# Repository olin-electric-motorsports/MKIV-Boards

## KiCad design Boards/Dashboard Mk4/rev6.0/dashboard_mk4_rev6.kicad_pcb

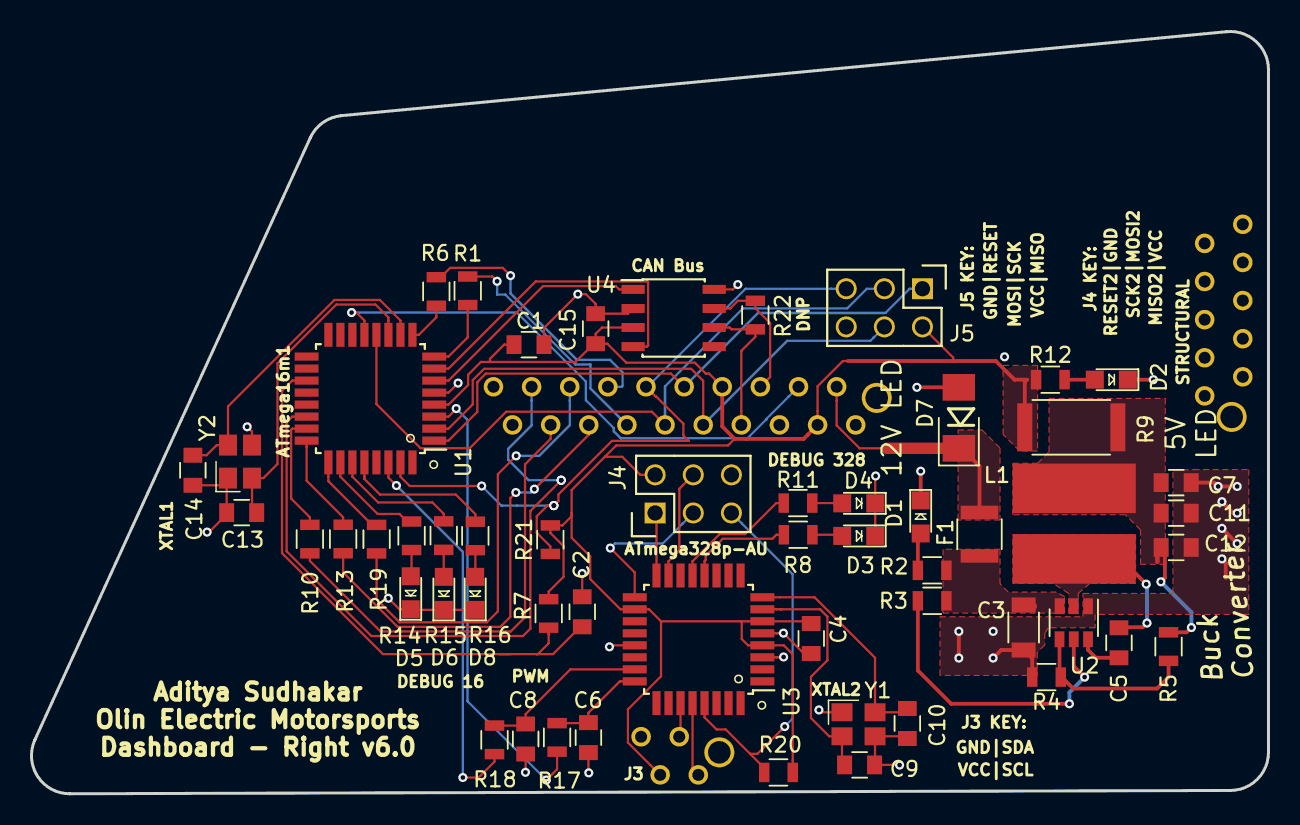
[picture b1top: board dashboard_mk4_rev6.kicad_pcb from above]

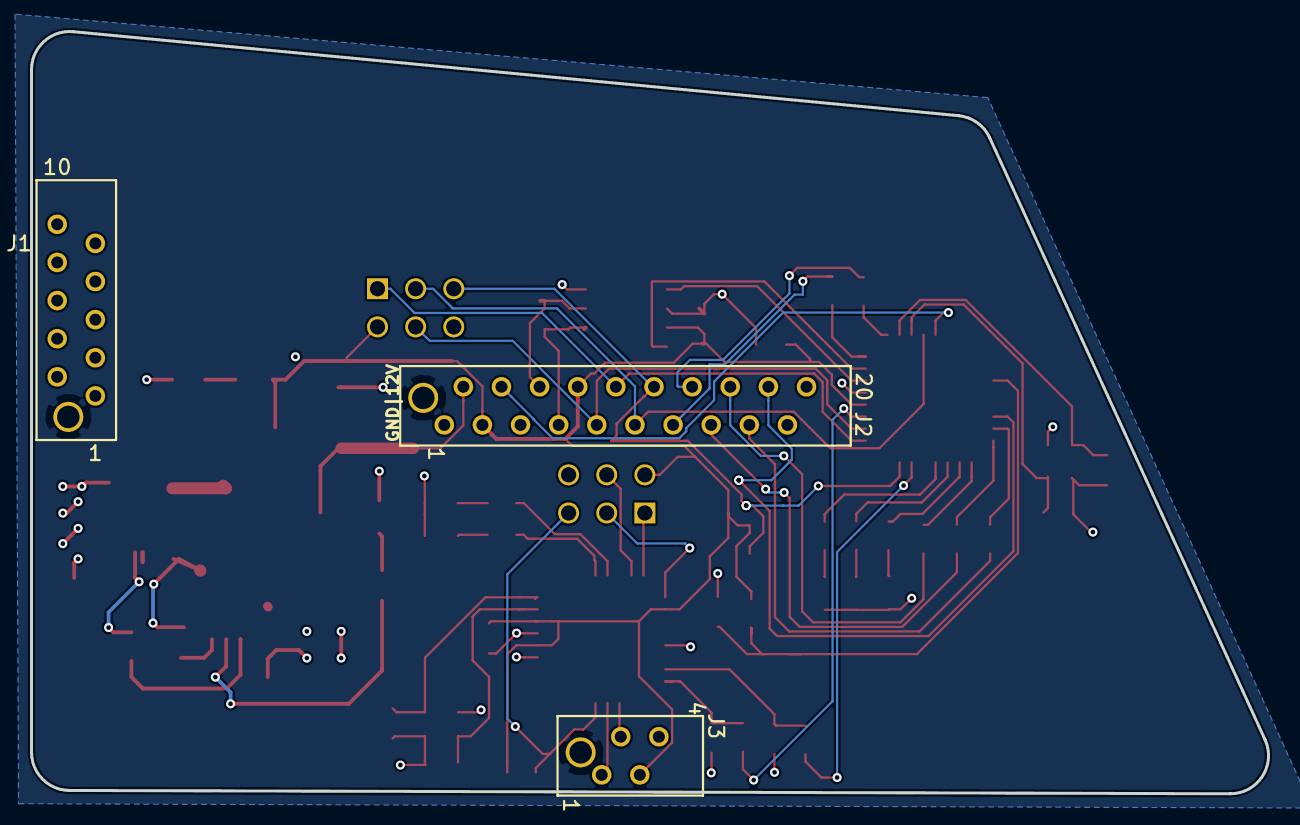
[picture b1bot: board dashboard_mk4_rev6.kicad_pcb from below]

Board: 2 copper layers, 82.4 x 50.8 mm, 58 parts (3 on the bottom side), 56 nets.

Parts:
C1, C4, C5, C6, C7, C8, C15: C_0.1uF; C_0805_OEM
C2: C_100pF; C_0805_OEM
C3: C_22uF; C_1206_OEM
C9, C10, C13, C14: C_30pF; C_0805_OEM
C11: C_1uF; C_0805_OEM
C12: C_47uF; C_0805_OEM
D1, D2: LED_0805; LED_0805_OEM
D3, D4, D5, D6, D8: LED; LED_0805_OEM
D7: D_Zener_18V; DO-214AA
F1: 500mA; Fuse_1210
J1: MM_F_VT_10; micromatch_female_vert_10
J2: MM_F_VT_20; micromatch_female_vert_20
J3: MM_F_VT_04; micromatch_female_vert_4
J4, J5: CONN_02X03; Pin_Header_Straight_2x03
L1: L_4.7uH; 4.7uH_Inductor_OEM
R1, R6, R8, R10, R11, R12, R13, R14, R15, R16, R19: R_200; R_0805_OEM
R2: R_1k; R_0805_OEM
R3, R4, R21: R_10k; R_0805_OEM
R5: R_51.1k; R_0805_OEM
R7: R_100; R_0805_OEM
R9: R_0_Jumper; R_2512_OEM
R17, R18: R_100K; R_0805_OEM
R20: R_10K; R_0805_OEM
R22: R_120; R_0805_OEM
U1: ATMEGA16M1; TQFP-32_7x7mm_Pitch0.8mm
U2: TPS561201; SOT-23-6_OEM
U3: ATmega328P-AU; TQFP-32_7x7mm_Pitch0.8mm
U4: CAN_Transceiver; SOIC-8_3.9x4.9mm_Pitch1.27mm_OEM
Y1, Y2: Crystal_SMD; Crystal_SMD_FA238

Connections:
+12V: D7.1, F1.1, J2.2
/12V_Fused: C3.1, F1.2, R2.1, R3.1, U2.3
/CANH: J2.6, R22.1, U4.7
/CANL: J2.7, R22.2, U4.6
/LED_BMS: J2.16, R19.2
/LED_IMD: J2.17, R10.1
/LED_START: J2.15, R13.1
/MISO: J2.10, J5.1, U1.1
/MISO_2: J4.1, U3.16
/MOSI: J2.9, J5.4, U1.2
/MOSI_2: J4.4, U3.15
/PWM_0: R18.1, U1.30
/PWM_1: R17.1, U1.3
/RESET: J2.12, J5.5, R21.1, U1.31
/RESET_2: J4.5, R20.1, U3.29
/RJLED1: J2.13, R1.1
/RJLED2: J2.14, R6.1
/RXCAN: U1.7, U4.4
/SCK: J2.11, J5.3, U1.12
/SCK_2: J4.3, U3.17
/SCL: J3.1, U3.28
/SDA: J3.2, U3.27
/START_BTN: J2.18, U1.22
/STR_POT_SENSE: J2.4, U1.13
/TXCAN: U1.6, U4.1
/XTAL1: C9.1, U3.7, Y1.1
/XTAL2: C10.1, U3.8, Y1.3
GND: C1.2, C2.2, C3.2, C4.2, C6.2, C7.2, C8.2, C9.2, C10.2, C11.2, C12.2, C13.2, C14.2, C15.2, D1.1, D2.1, D3.1, D4.1, D5.1, D6.1, D7.2, D8.1, J2.1, J2.5, J3.4, J4.6, J5.6, R4.2, U1.5, U2.1, U3.3, U3.5, U3.21, U4.2, U4.8, Y1.2, Y1.4, Y2.2, Y2.4
unnamed: C2.1, R7.2, U1.19
unnamed: C5.1, U2.6
unnamed: C5.2, L1.1, U2.2
unnamed: C6.1, R17.2, U3.24
unnamed: C8.1, R18.2, U3.23
unnamed: C7.1, C11.1, C12.1, L1.2, R5.2, R9.2
unnamed: C13.1, U1.11, Y2.1
unnamed: C14.1, U1.10, Y2.3
unnamed: D1.2, R2.2
unnamed: D2.2, R12.2
unnamed: D3.2, R8.1
unnamed: D4.2, R11.1
unnamed: D5.2, R14.2
unnamed: D6.2, R15.2
unnamed: D8.2, R16.2
unnamed: R1.2, U1.8
unnamed: R3.2, U2.5
unnamed: R4.1, R5.1, U2.4
unnamed: R6.2, U1.9
unnamed: R8.2, U3.12
unnamed: R10.2, U1.23
unnamed: R11.2, U3.13
unnamed: R13.2, U1.24
unnamed: R14.1, U1.26
unnamed: R15.1, U1.27
unnamed: R16.1, U1.28
unnamed: R19.1, U1.25
VCC: C1.1, C4.1, C15.1, J2.3, J2.8, J3.3, J4.2, J5.2, R7.1, R9.1, R12.1, R20.2, R21.2, U1.4, U3.4, U3.6, U3.18, U4.3

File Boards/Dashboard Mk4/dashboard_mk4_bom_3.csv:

Component,Description,Part,References,Value,Footprint,Quantity Per PCB,Datasheet,Package,MPN,MFN,PurchasingLink
1,"Capacitor, 0.1uF, 50V, 5%, 0805",C_0.1uF,C1 C4 C5 C6 C7 C8 C15,C_0.1uF,C_0805_OEM,7,http://datasheets.avx.com/X7RDielectric.pdf,Value,478-3352-1-ND,DK,https://www.digikey.com/products/en?keywords=478-3352-1-ND
2,"Capacitor, 100pF, 50V, 5%, 0805",C_100pF,C2,C_100pF,C_0805_OEM,1,https://katalog.we-online.de/pbs/datasheet/885012007057.pdf,Value,732-7852-1-ND,DK,https://www.digikey.com/product-detail/en/wurth-electronics-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
3,"Capacitor, 1uF, 25V, 10%, 0805",C_1uF,C11,C_1uF,C_0805_OEM,1,http://www.samsungsem.com/kr/support/product-search/mlcc/__i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,Value,1276-2887-1-ND,DK,https://www.digikey.com/product-detail/en/samsung-electro-me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
4,"Capacitor, 22uF, 16V, 20%, 1206",C_22uF,C3,C_22uF,C_1206_OEM,1,https://product.tdk.com/info/en/catalog/datasheets/mlcc_comm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,Value,445-11693-1-ND,DK,https://www.digikey.com/product-detail/en/tdk-corporation/C3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
5,"Capacitor, 30pF, 50V, 5%, 0805",C_30pF,C9 C10 C13 C14,C_30pF,C_0805_OEM,4,https://media.digikey.com/pdf/Data%20Sheets/Samsung%20PDFs/C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,Value,1276-1130-1-ND,DK,https://www.digikey.com/product-detail/en/samsung-electro-me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
6,"Capacitor, 47uF, 6.3V, 20%, 0805",C_47uF,C12,C_47uF,C_0805_OEM,1,http://www.samsungsem.com/kr/support/product-search/mlcc/__i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,Value,1276-6467-1-ND,DK,https://www.digikey.com/product-detail/en/samsung-electro-me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
7,"Diode, Zener, 18V, 5W, 5%",D_Zener_18V,D7,D_Zener_18V,DO-214AA,1,http://www.mccsemi.com/up_pdf/SMBJ5338B-SMBJ5388B(SMB).pdf,DO-214AA (SMB),SMBJ5355B-TPMSCT-ND,DK,https://www.digikey.com/products/en?keywords=SMBJ5355B-TPMSCT-ND
8,Light emitting diode,LED,D3 D4 D5 D6 D8,LED,LED_0805_OEM,5,,,,,
9,"LED, Green, 2.2V, 20mA, 0805",LED_0805,D1 D2,LED_0805,LED_0805_OEM,2,http://www.osram-os.com/Graphics/XPic9/00078860_0.pdf,Value,475-1410-1-ND,DK,https://www.digikey.com/products/en?keywords=475-1410-1-ND
10,"Fuse, PTC, 500mA, 16V, 1210",F_500mA_16V,F1,500mA,Fuse_1210,1,https://belfuse.com/resources/CircuitProtection/datasheets/0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,Value,507-1786-1-ND,DK,https://www.digikey.com/product-detail/en/bel-fuse-inc/0ZCH0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
11,"Connector header through hole 2x3 0.100"" (2.54mm)",CONN_02X03,J4 J5,CONN_02X03,Pin_Header_Straight_2x03,2,http://portal.fciconnect.com/Comergent//fci/drawing/67996.pdf,Value,609-3234-ND,DK,https://www.digikey.com/product-detail/en/amphenol-fci/67997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
12,Micro-MaTch connector 4 pin female vertical,MM_F_VT_04,J3,MM_F_VT_04,micromatch_female_vert_4,1,http://www.te.com/commerce/DocumentDelivery/DDEController?Ac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,,338068-4,TE,http://www.te.com/global-en/product-338068-4.html
13,Micro-MaTch connector 10 pin female vertical,MM_F_VT_10,J1,MM_F_VT_10,micromatch_female_vert_10,1,http://www.te.com/commerce/DocumentDelivery/DDEController?Ac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,,1-338068-0,TE,http://www.te.com/global-en/product-1-338068-0.html
14,Micro-MaTch connector 20 pin female vertical,MM_F_VT_20,J2,MM_F_VT_20,micromatch_female_vert_20,1,http://www.te.com/commerce/DocumentDelivery/DDEController?Ac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,,2-338068-0,TE,http://www.te.com/global-en/product-2-338068-0.html
15,"Inductor, 4.7uH, 4.4A, 25mOhm, 20%",L_4.7uH,L1,L_4.7uH,4.7uH_Inductor_OEM,1,https://product.tdk.com/info/en/documents/wdcatalog/withdraw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,Value,445-6583-1-ND,DK,https://www.digikey.com/product-detail/en/tdk-corporation/VL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
16,"Resistor, 0 ohm jumper, 0.1W, 0603",R_0,R9,R_0_Jumper,R_0603_1608Metric,1,http://industrial.panasonic.com/www-cgi/jvcr13pz.cgi?E+PZ+3+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,Value,P0.0GCT-ND,DK,https://www.digikey.com/product-detail/en/panasonic-electron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
17,"Resistor, 100, 0.25W, 1%, 0805",R_100,R7,R_100,R_0805_OEM,1,https://www.seielect.com/Catalog/SEI-rncp.pdf,Value,RNCP0805FTD100RCT-ND,DK,https://www.digikey.com/products/en?keywords=RNCP0805FTD100RCT-ND
18,"Resistor, 100K, 0.125W, 1%, 0805",R_100K,R17 R18,R_100K,R_0805_OEM,2,https://industrial.panasonic.com/cdbs/www-data/pdf/RDA0000/A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,,P100KCCT-ND,DK,https://www.digikey.com/product-detail/en/panasonic-electron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
19,"Resistor, 10K, 0.25W, 1%, 0805",R_10K,R20 R21,R_10K,R_0805_OEM,2,http://www.bourns.com/data/global/pdfs/CRS.pdf,Value,CRS0805-FX-1002ELFCT-ND,DK,https://www.digikey.com/products/en?keywords=CRS0805-FX-1002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
20,"Resistor, 10K, 5W, 1%, Axial",R_10K_HV,R3 R4,R_10k,R_1K_HV,2,http://www.vishay.com/docs/28731/pacserie.pdf,Value,PPC5D10.0KCT-ND,DK,https://www.digikey.com/products/en?keywords=PPC5D10.0KCT-ND
21,"Resistor, 200, 0.125W, 5%, 0805",R_200,R22,R_120,R_0805_OEM,1,https://www.seielect.com/Catalog/SEI-RMCF_RMCP.pdf,Value,RMCF0805JT200RCT-ND,DK,https://www.digikey.com/products/en?keywords=RMCF0805JT200RCT-ND
22,"Resistor, 1K, 0.25W, 1%, 0805",R_1K,R2,R_1k,R_0805_OEM,1,https://www.seielect.com/Catalog/SEI-rncp.pdf,Value,RNCP0805FTD1K00CT-ND,DK,https://www.digikey.com/products/en?keywords=RNCP0805FTD1K00CT-ND
23,"Resistor, 200, 0.125W, 5%, 0805",R_200,R1 R6 R8 R10 R11 R12 R13 R14 R15 R16 R19,R_200,R_0805_OEM,11,https://www.seielect.com/Catalog/SEI-RMCF_RMCP.pdf,Value,RMCF0805JT200RCT-ND,DK,https://www.digikey.com/products/en?keywords=RMCF0805JT200RCT-ND
24,"Resistor, 51.1K, 0.125W, 1%, 0805",R_51.1K,R5,R_51.1k,R_0805_OEM,1,https://industrial.panasonic.com/cdbs/www-data/pdf/RDA0000/A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,Value,P51.1KCCT-ND,DK,https://www.digikey.com/product-detail/en/panasonic-electron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
25,"Microcontroller, 8-bit, 1KB RAM, 16KB Flash",ATMEGA16M1,U1,ATMEGA16M1,TQFP-32_7x7mm_Pitch0.8mm,1,http://ww1.microchip.com/downloads/en/DeviceDoc/Atmel-8209-8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,,ATMEGA16M1-AU-ND,DK,https://www.digikey.com/product-detail/en/atmel/ATMEGA16M1-A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
26,"Microcontroller, 8-bit, 1KB RAM, 16KB Flash",ATmega328P-AU,U3,ATmega328P-AU,TQFP-32_7x7mm_Pitch0.8mm,1,http://ww1.microchip.com/downloads/en/DeviceDoc/Atmel-7810-A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,,ATMEGA328P-AURCT-ND,,https://www.digikey.com/product-detail/en/microchip-technolo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
27,"High speed CAN transceiver, 1Mb/s",MCP2561-E_SN,U4,CAN_Transceiver,SOIC-8_3.9x4.9mm_Pitch1.27mm_OEM,1,http://www.microchip.com/mymicrochip/filehandler.aspx?ddocna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,Value,MCP2561-E/SN-ND,DK,https://www.digikey.com/products/en?keywords=mcp2561-e%2Fsn
28,"Buck converter, 4.5-17V input, adj 0.76-7V output, 1A, 580kHz",TPS561201,U2,TPS561201,SOT-23-6_OEM,1,http://www.ti.com/lit/ds/symlink/tps561201.pdf,Value,TPS561201,DK,https://www.digikey.com/products/en?keywords=296-46928-1-ND
29,CRYSTAL 16.0000MHZ 18PF SMD,Crystal_SMD,Y1 Y2,Crystal_SMD,Crystal_SMD_FA238,2,http://www.txccorp.com/download/products/quartz_crystals/201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,Value,887-1125-1-ND,DK,https://www.digikey.com/product-detail/en/txc-corporation/7M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





Component Groups:,29
Component Count:,58
Fitted Components:,58
Number of PCBs:,1
Total components:,58
Schematic Version:,3
Schematic Date:,
BoM Date:,Tue 20 Nov 2018 10:55:47 AM EST
Schematic Source:,/home/asudhakar/Documents/Forumla/MKIV-Boards/Boards/Dashboard Mk4/dashboard_mk4.sch
KiCad Version:,Eeschema 5.0.1-33cea8e~68~ubuntu18.04.1

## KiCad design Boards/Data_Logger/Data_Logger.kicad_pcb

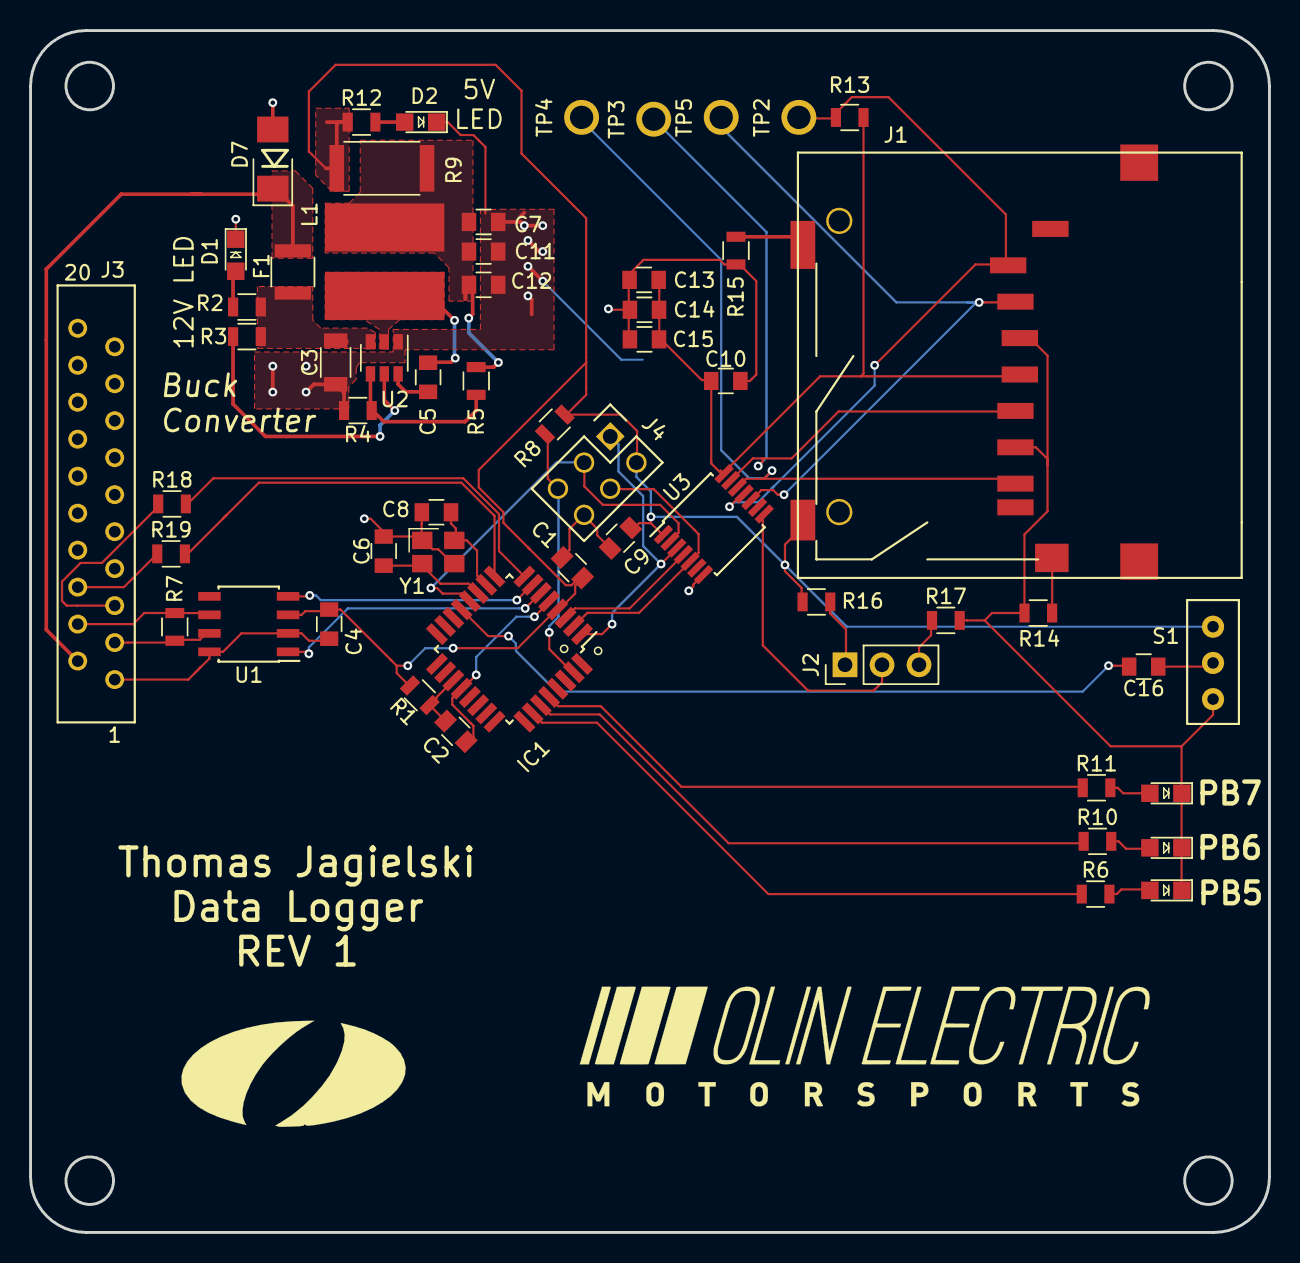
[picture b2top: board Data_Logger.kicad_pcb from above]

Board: 2 copper layers, 85.1 x 82.6 mm, 57 parts (0 on the bottom side), 45 nets.

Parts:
C1, C4, C5, C9, C10, C12, C15, C16: C_0.1uF; C_0805_OEM
C2: C_100pF; C_0805_OEM
C3: C_22uF; C_1206_OEM
C6, C8: C_30pF; C_0805_OEM
C7: C_47uF; C_0805_OEM
C11, C14: C_1uF; C_0805_OEM
C13: C_10uF; C_0805_OEM
D1, D2, D3, D4, D5: LED_0805; LED_0805_OEM
D7: D_Zener_18V; DO-214AA
F1: 500mA; Fuse_1210
IC1: ATMEGA16M1; TQFP-32_7x7mm_Pitch0.8mm
J1: SD_socket; sd_socket_molex_5009980900
J2: Conn_01x03; PinHeader_1x03_P2.54mm_Vertical
J3: MM_F_RA_20; micromatch_female_ra_20
J4: CONN_02X03; Pin_Header_Straight_2x03
L1: L_4.7uH; 4.7uH_Inductor_OEM
R1: R_100; R_0805_OEM
R2: R_1k; R_0805_OEM
R3, R4, R8: R_10k; R_0805_OEM
R5: R_51.1k; R_0805_OEM
R6, R10, R11, R12, R18, R19: R_200; R_0805_OEM
R7: R_120; R_0805_OEM
R9: R_0_Jumper; R_2512_OEM
R13, R14, R15, R16, R17: R_10K; R_0805_OEM
S1: MHSS1105
TP2, TP3, TP4, TP5: TP; tp_1.6mm
U1: CAN_Transceiver; SOIC-8_3.9x4.9mm_Pitch1.27mm_OEM
U2: TPS561201; SOT-23-6_OEM
U3: TXB0104; TSSOP-14_4.4x5mm_P0.65mm
Y1: Crystal_SMD; Crystal_SMD_FA238

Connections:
+3V3: C10.1, C13.1, C14.1, C15.1, J1.4, R13.1, U3.14
+12V: D7.1, F1.1, J3.2
/12V_Fused: C3.1, F1.2, R2.1, R3.1, U2.3
/CANH: J3.3, R7.1, U1.7
/CANL: J3.4, R7.2, U1.6
/LED_1: J3.5, R18.1
/LED_2: J3.6, R19.1
/MISO: IC1.1, J4.1, U3.3
/MISO_3V3: J1.7, TP4.1, U3.12
/MOSI: IC1.2, J4.4, U3.5
/MOSI_3V3: J1.2, TP5.1, U3.10
/PLED1: IC1.26, R6.1
/PLED2: IC1.27, R10.1
/PLED3: IC1.28, R11.1
/RESET: IC1.31, J4.5, R8.2
/RXCAN: IC1.7, U1.4
/SCK: IC1.12, J4.3, U3.2
/SCK_3V3: J1.5, TP3.1, U3.13
/SS: IC1.3, U3.4
/SS_3V3: J1.1, R13.2, TP2.1, U3.11
/SWITCH: C16.2, IC1.13
/TXCAN: IC1.6, U1.1
GND: C1.2, C2.2, C3.2, C4.2, C6.2, C7.2, C8.2, C9.2, C10.2, C11.2, C12.2, C13.2, C14.2, C15.2, D1.1, D2.1, D3.1, D4.1, D5.1, D7.2, IC1.5, IC1.20, J1.3, J1.6, J3.1, J4.6, R4.2, R14.2, R15.2, R17.2, S1.3, U1.2, U1.8, U2.1, U3.7, Y1.2, Y1.4
unnamed: C2.1, IC1.19, R1.2
unnamed: C5.1, U2.6
unnamed: C5.2, L1.1, U2.2
unnamed: C6.1, IC1.11, Y1.1
unnamed: C8.1, IC1.10, Y1.3
unnamed: C7.1, C11.1, C12.1, L1.2, R5.2, R9.2
unnamed: C16.1, S1.2
unnamed: D1.2, R2.2
unnamed: D2.2, R12.2
unnamed: D3.2, R6.2
unnamed: D4.2, R10.2
unnamed: D5.2, R11.2
unnamed: IC1.8, R18.2
unnamed: IC1.9, R19.2
unnamed: J1.11, R14.1
unnamed: J1.12, R15.1
unnamed: J2.1, R16.2
unnamed: J2.2, U3.8
unnamed: J2.3, R17.1
unnamed: R3.2, U2.5
unnamed: R4.1, R5.1, U2.4
VCC: C1.1, C4.1, C9.1, IC1.4, J1.10, J4.2, R1.1, R8.1, R9.1, R12.1, R16.1, S1.1, U1.3, U3.1

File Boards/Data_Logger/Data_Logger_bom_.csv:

Component,Description,Part,References,Value,Footprint,Quantity Per PCB,Datasheet,Package,MPN,MFN,PurchasingLink,Purchasing Link
1,"Capacitor, 0.1uF, 50V, 5%, 0805",C_0.1uF,C1 C4 C5 C9 C10 C12 C15 C16,C_0.1uF,C_0805_OEM,8,http://datasheets.avx.com/X7RDielectric.pdf,Value,478-3352-1-ND,Digi-Key DK,https://www.digikey.com/products/en?keywords=478-3352-1-ND,
2,"Capacitor, 100pF, 50V, 5%, 0805",C_100pF,C2,C_100pF,C_0805_OEM,1,https://content.kemet.com/datasheets/KEM_C1003_C0G_SMD.pdf,Value,399-1122-1-ND,Digi-Key,https://www.digikey.com/product-detail/en/kemet/C0805C101J5G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,
3,"Capacitor, 10uF, 10V, 10%, 0805",C_10uF,C13,C_10uF,C_0805_OEM,1,http://www.samsungsem.com/kr/support/product-search/mlcc/__i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,,1276-1052-1-ND,DK,https://www.digikey.com/product-detail/en/samsung-electro-me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,
4,"Capacitor, 1uF, 25V, 10%, 0805",C_1uF,C11 C14,C_1uF,C_0805_OEM,2,http://datasheets.avx.com/X7RDielectric.pdf,Value,478-10487-1-ND 1276-2887-1-ND,Digi-Key DK,https://www.digikey.com/product-detail/en/avx-corporation/08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 https://www.digikey.com/product-detail/en/samsung-electro-me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,
5,"Capacitor, 22uF, 16V, 20%, 1206",C_22uF,C3,C_22uF,C_1206_OEM,1,http://www.samsungsem.com/kr/support/product-search/mlcc/__i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,Value,1276-2725-1-ND,Digi-Key,https://www.digikey.com/products/en?keywords=1276-2725-1-ND,
6,"Capacitor, 30pF, 50V, 5%, 0805",C_30pF,C6 C8,C_30pF,C_0805_OEM,2,https://media.digikey.com/pdf/Data%20Sheets/Samsung%20PDFs/C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,Value,1276-1130-1-ND,Digi-Key,https://www.digikey.com/product-detail/en/samsung-electro-me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,
7,"Capacitor, 47uF, 6.3V, 20%, 0805",C_47uF,C7,C_47uF,C_0805_OEM,1,http://www.yuden.co.jp/productdata/catalog/en/mlcc_all_e.pdf,Value,587-4280-1-ND,Digi-Key,https://www.digikey.com/product-detail/en/taiyo-yuden/JMK212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,
8,"Diode, Zener, 18V, 5W, 5%",D_Zener_18V,D7,D_Zener_18V,DO-214AA,1,http://www.mccsemi.com/up_pdf/SMBJ5338B-SMBJ5388B(SMB).pdf,DO-214AA (SMB),SMBJ5355B-TPMSCT-ND,Digi-Key,https://www.digikey.com/products/en?keywords=SMBJ5355B-TPMSCT-ND,
9,"LED, Green, 2.2V, 20mA, 0805",LED_0805,D1 D2 D3 D4 D5,LED_0805,LED_0805_OEM,5,http://www.osram-os.com/Graphics/XPic9/00078860_0.pdf,Value,475-1410-1-ND,Digi-Key DK,https://www.digikey.com/products/en?keywords=475-1410-1-ND,
10,"Fuse, PTC, 500mA, 16V, 1210",F_500mA_16V,F1,500mA,Fuse_1210,1,https://belfuse.com/resources/CircuitProtection/datasheets/0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,Value,507-1786-1-ND,Digi-Key,https://www.digikey.com/product-detail/en/bel-fuse-inc/0ZCH0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,
11,"Microcontroller, 8-bit, 1KB RAM, 16KB Flash",ATMEGA16M1,IC1,ATMEGA16M1,TQFP-32_7x7mm_Pitch0.8mm,1,http://www.atmel.com/Images/Atmel-8209-8-bit%20AVR%20ATmega1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,Value,ATMEGA16M1-AU-ND,Digi-Key,https://www.digikey.com/product-detail/en/atmel/ATMEGA16M1-A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,
12,"Connector header through hole 2x3 0.100"" (2.54mm)",CONN_02X03,J4,CONN_02X03,Pin_Header_Straight_2x03,1,http://portal.fciconnect.com/Comergent//fci/drawing/67996.pdf,Value,609-3234-ND,Digi-Key,https://www.digikey.com/product-detail/en/amphenol-fci/67997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,
13,"Generic connector, single row, 01x03, script generated (kicad-library-utils/schlib/autogen/connector/)",Conn_01x03,J2,Conn_01x03,PinHeader_1x03_P2.54mm_Vertical,1,~,,,,,
14,Micro-MaTch connector 20 pin female right angle,MM_F_RA_20,J3,MM_F_RA_20,micromatch_female_ra_20,1,http://www.te.com/commerce/DocumentDelivery/DDEController?Ac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,,2-338070-0,TE,http://www.te.com/usa-en/product-2-338070-0.html,
15,SD card socket with detect switch,SD_socket,J1,SD_socket,sd_socket_molex_5009980900,1,https://www.molex.com/pdm_docs/sd/5009980900_sd.pdf,,WM24032CT-ND,DK,https://www.digikey.com/product-detail/en/molex-llc/50099809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,
16,"Inductor, 4.7uH, 4.4A, 25mOhm, 20%",L_4.7uH,L1,L_4.7uH,4.7uH_Inductor_OEM,1,https://product.tdk.com/info/en/documents/wdcatalog/withdraw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,Value,445-6583-1-ND,Digi-Key,https://www.digikey.com/product-detail/en/tdk-corporation/VL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,
17,"Resistor, 0 ohm jumper, 0.1W, 0603",R_0,R9,R_0_Jumper,R_2512_OEM,1,http://www.te.com/commerce/DocumentDelivery/DDEController?Ac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,Value,A121322CT-ND,Digi-Key,https://www.digikey.com/products/en?keywords=A121322CT-ND,
18,"Resistor, 100, 0.25W, 1%, 0805",R_100,R1,R_100,R_0805_OEM,1,https://www.seielect.com/Catalog/SEI-rncp.pdf,Value,RNCP0805FTD100RCT-ND,Digi-Key,https://www.digikey.com/products/en?keywords=RNCP0805FTD100RCT-ND,
19,"Resistor, 10K, 0.25W, 1%, 0805",R_10K,R8 R13 R14 R15 R16 R17,R_10k,R_0805_OEM,6,http://www.bourns.com/data/global/pdfs/CRS.pdf,Value,CRS0805-FX-1002ELFCT-ND,Digi-Key DK,https://www.digikey.com/products/en?keywords=CRS0805-FX-1002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,
20,"Resistor, 10K, 5W, 1%, Axial",R_10K_HV,R3 R4,R_10k,R_0805_OEM,2,http://www.bourns.com/data/global/pdfs/CRS.pdf,Value,CRS0805-FX-1002ELFCT-ND,Digi-Key,https://www.digikey.com/products/en?keywords=CRS0805-FX-1002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,
21,"Resistor, 120, 0.125W, 1%, 0805",R_120,R7,R_120,R_0805_OEM,1,https://www.mouser.com/datasheet/2/315/AOA0000C304-1149620.pdf,,667-ERJ-6ENF1200V,DK,https://www.mouser.com/ProductDetail/Panasonic-Industrial-De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,
22,"Resistor, 1K, 0.25W, 1%, 0805",R_1K,R2,R_1k,R_0805_OEM,1,https://www.seielect.com/Catalog/SEI-rncp.pdf,Value,RNCP0805FTD1K00CT-ND,Digi-Key,https://www.digikey.com/products/en?keywords=RNCP0805FTD1K00CT-ND,
23,"Resistor, 200, 0.125W, 5%, 0805",R_200,R6 R10 R11 R12 R18 R19,R_200,R_0805_OEM,6,https://www.seielect.com/Catalog/SEI-RMCF_RMCP.pdf,Value,RMCF0805JT200RCT-ND,DK Digi-Key,https://www.digikey.com/products/en?keywords=RMCF0805JT200RCT-ND,
24,"Resistor, 51.1K, 0.125W, 1%, 0805",R_51.1K,R5,R_51.1k,R_0805_OEM,1,http://www.yageo.com.tw/exep/pages/download/literatures/PYu-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,Value,311-51.1KCRCT-ND,Digi-Key,https://www.digikey.com/products/en?keywords=311-51.1KCRCT-ND,
25,Slider Switch,MHSS1105,S1,MHSS1105,MHSS1105,1,https://www.apem.com/us/index.php?controller=attachment&id_a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,,679-1849-ND,APEM Inc.,,https://www.digikey.com/product-detail/en/apem-inc/MHSS1105/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
26,"High speed CAN transceiver, 1Mb/s",MCP2561-E_SN,U1,CAN_Transceiver,SOIC-8_3.9x4.9mm_Pitch1.27mm_OEM,1,http://www.microchip.com/mymicrochip/filehandler.aspx?ddocna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,Value,MCP2561-E/SN-ND,Digi-Key,https://www.digikey.com/products/en?keywords=mcp2561-e%2Fsn,
27,"Buck converter, 4.5-17V input, adj 0.76-7V output, 1A, 580kHz",TPS561201,U2,TPS561201,SOT-23-6_OEM,1,http://www.ti.com/lit/ds/symlink/tps561201.pdf,Value,TPS561201,Digi-Key,https://www.digikey.com/products/en?keywords=296-46928-1-ND,
28,"Voltage level translator, 4-channel, bidirectional, TSSOP-14",TXB0104,U3,TXB0104,TSSOP-14_4.4x5mm_P0.65mm,1,http://www.ti.com/lit/ds/symlink/txb0104.pdf,,296-21929-1-ND,DK,https://www.digikey.com/product-detail/en/texas-instruments/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,
29,CRYSTAL 16.0000MHZ 18PF SMD,Crystal_SMD,Y1,Crystal_SMD,Crystal_SMD_FA238,1,https://support.epson.biz/td/api/doc_check.php?dl=brief_FA-2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,Value,SER3686CT-ND,Digi-Key,https://www.digikey.com/products/en?keywords=SER3686CT-ND,





Component Groups:,29
Component Count:,53
Fitted Components:,53
Number of PCBs:,1
Total components:,53
Schematic Version:,
Schematic Date:,
BoM Date:,Thu 31 Jan 2019 08:48:02 PM EST
Schematic Source:,/home/thomas/Documents/Formula/MKIV-Boards/Boards/Data_Logger/Data_Logger.sch
KiCad Version:,Eeschema 5.0.2-bee76a0~70~ubuntu18.04.1

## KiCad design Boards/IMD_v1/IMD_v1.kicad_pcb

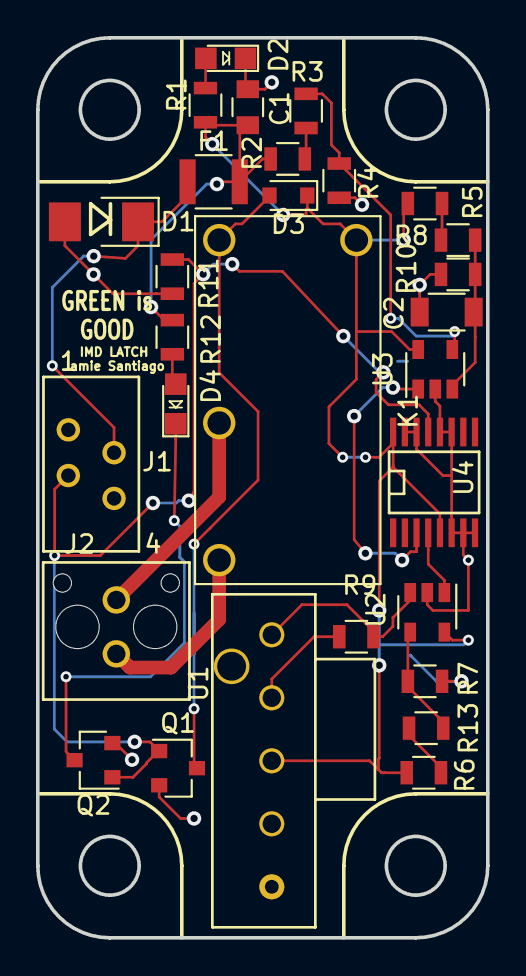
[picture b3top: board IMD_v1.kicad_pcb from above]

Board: 2 copper layers, 25.0 x 50.0 mm, 29 parts (0 on the bottom side), 19 nets.

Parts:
C1: C_10uF_16V; C_0805_OEM
C2: C_22uF; C_1206_OEM
D1: D_Zener_18V; DO-214AA
D2, D4: LED_0805; LED_0805_OEM
D3: D_Schottky_Small; D_0805_OEM
F1: F_500mA_16V; Fuse_1210
J1: MM_F_RA_04; micromatch_female_ra_4
J2: MicroFit_V_2
K1: G5Q-1A4-DC5-5V; Relay_SPST_OMRON-G5Q-1A4_OEM
Q1, Q2: SSM3K333R; SOT-23F
R1, R5, R12: R_1K; R_0805_OEM
R2, R6, R9: R_2.2K; R_0805_OEM
R3, R13: R_300K; R_0805_OEM
R4, R7, R10, R11: R_604K; R_0805_OEM
R8: R_120K; R_0805_OEM
U1: Ultrafit_5(IMD); Ultrafit_5
U2, U3: TLV3701QDBVRG4Q1; SOT-23-5_OEM
U4: CD4044BPWR; TSSOP-16-OEM

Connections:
+12V: D1.1, F1.1, J1.2
/12V_Fused: C1.1, D3.1, F1.2, K1.5, R1.1, R2.1, R5.1, R6.1, R12.1, U1.3, U2.5, U3.5, U4.5, U4.16
/IMD_Status_Output: J1.3, Q1.1, Q2.1, R11.1, U4.13
/delay_side_out: U3.1, U4.3
/imd_side_out: U2.1, U4.4
GND: C1.2, C2.2, D1.2, D2.1, J1.1, J1.4, Q1.2, Q2.2, R4.2, R7.2, R9.2, R10.2, R11.2, U1.2, U1.4, U1.5, U2.2, U3.2, U4.6, U4.7, U4.8, U4.11, U4.12, U4.14, U4.15
unnamed: C2.1, R8.1, R10.1, U3.3
unnamed: D2.2, R1.2
unnamed: D3.2, K1.1, Q1.3
unnamed: D4.1, Q2.3
unnamed: D4.2, R12.2
unnamed: J2.1, K1.3
unnamed: J2.2, K1.2
unnamed: R2.2, R3.1
unnamed: R3.2, R4.1, U3.4
unnamed: R5.2, R8.2
unnamed: R9.1, U1.1, U2.3
unnamed: R6.2, R13.1
unnamed: R7.1, R13.2, U2.4

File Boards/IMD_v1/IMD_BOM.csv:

Id,Designator,Package,Quantity,Designation,Supplier and ref,
1,K1,Relay_SPST_OMRON-G5Q-1A4_OEM,1,G5Q-1A4-DC5-5V,,Last
2,C1,C_0805_OEM,1,C_10uF_16V,,
3,C2,C_1206_OEM,1,C_22uF,,
4,D1,DO-214AA,1,D_Zener_18V,,
5,"D2,D4",LED_0805_OEM,2,LED_0805,,
6,D3,D_0805_OEM,1,D_Schottky_Small,,No
7,F1,Fuse_1210,1,F_500mA_16V,,No
8,J1,micromatch_female_ra_4,1,MM_F_RA_04,,Last
9,J2,Ultrafit_2,1,UF_2_VT,,Last
10,"Q1,Q2",SOT-23F,2,SSM3K333R,,
11,"R1,R5,R12",R_0805_OEM,3,R_1K,,
12,"R2,R6,R9",R_0805_OEM,3,R_2.2K,,
13,"R3,R13",R_0805_OEM,2,R_300K,,
14,"R4,R7,R10,R11",R_0805_OEM,4,R_604K,,
15,R8,R_0805_OEM,1,R_120K,,
16,U1,Ultrafit_5,1,Ultrafit_5(IMD),,Last
17,"U2,U3",SOT-23-5_OEM,2,TLV3701QDBVRG4Q1,,No
18,U4,TSSOP-16-OEM,1,CD4044BPWR,,No

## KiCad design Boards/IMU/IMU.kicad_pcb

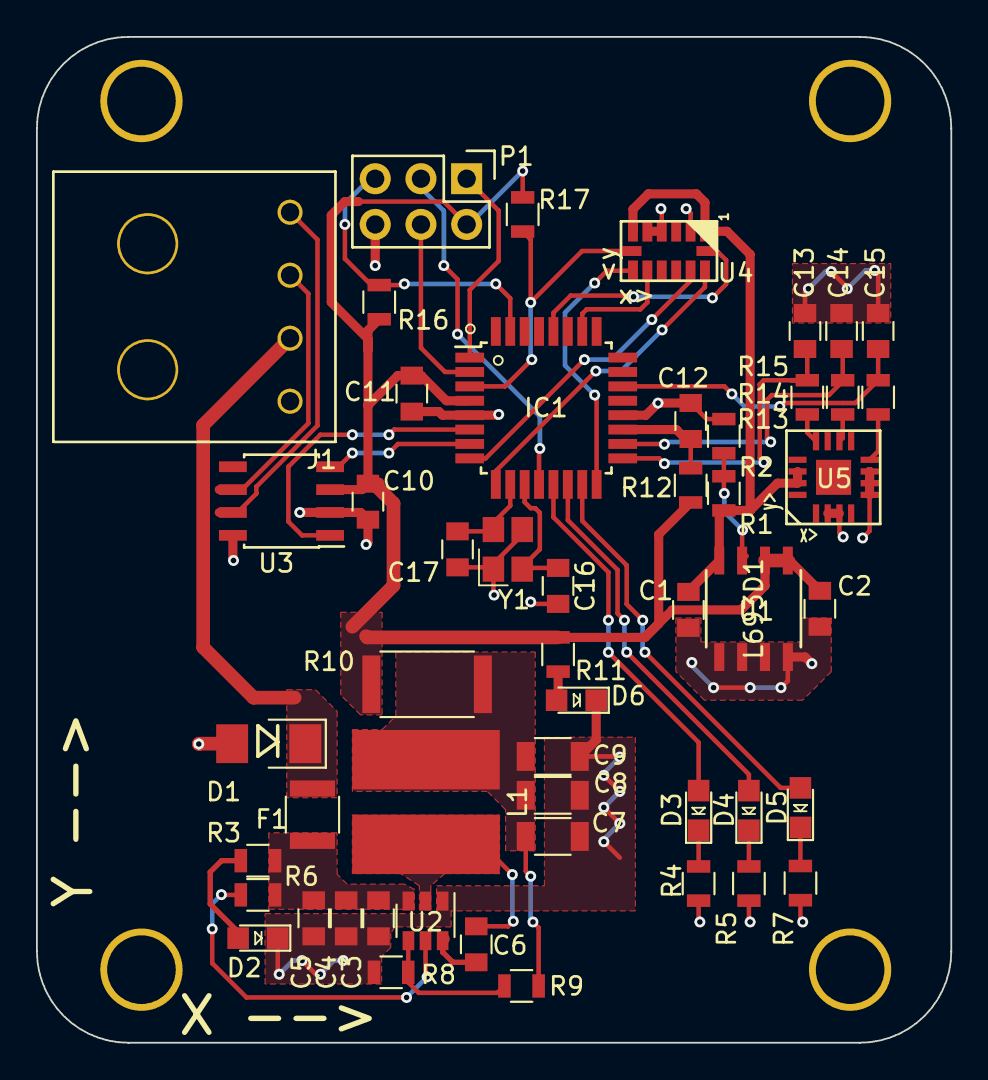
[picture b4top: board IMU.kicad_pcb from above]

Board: 2 copper layers, 50.8 x 55.9 mm, 51 parts (0 on the bottom side), 42 nets.

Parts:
C1, C2, C4, C5: C_10uF; C_0805_OEM
C3, C6, C10, C11: C_0.1uF; C_0805_OEM
C7, C8, C9: C_22uF; C_1206_OEM
C12: C_100pF; C_0805_OEM
C13, C14, C15: C_0.33uF; C_0805_OEM
C16, C17: C_30pF; C_0805_OEM
D1: D_Zener_18V; DO-214AA
D2, D3, D4, D5, D6: LED_0805; LED_0805_OEM
F1: F_500mA_16V; Fuse_1210
IC1: ATMEGA16M1; TQFP-32_7x7mm_Pitch0.8mm
J1: Ultrafit_4_RA
L1: L_4.7uH; 4.7uH_Inductor_OEM
P1: CONN_02X03; Pin_Header_Straight_2x03
R1: R_178k; R_0805_OEM
R2: R_120k; R_0805_OEM
R3: R_1k; R_0805_OEM
R4, R5, R7, R11: R_200; R_0805_OEM
R6, R8, R16, R17: R_10k; R_0805_OEM
R9: R_55.1k; R_0805_OEM
R10: R_0_Jumper; R_2512_OEM
R12: R_100; R_0805_OEM
R13, R14, R15: R_30.1k; R_0805_OEM
U1: L693D1; L6932D1.2TR
U2: TPS561201; SOT-23-6_OEM
U3: CAN_Transceiver; SOIC-8_3.9x4.9mm_Pitch1.27mm_OEM
U4: ADXL345
U5: ADXL335
Y1: Crystal_SMD; Crystal_SMD_FA238

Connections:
/2.98V: C1.1, R1.1, U1.4, U4.1, U4.6, U5.14, U5.15
/12V: D1.1, F1.2, J1.2
/CANH: J1.4, U3.7
/CANL: J1.3, U3.6
/INT1: IC1.16, U4.8
/INT2: IC1.26, U4.9
/MISO: IC1.8, U4.12
/MISO-P: IC1.1, P1.1
/MOSI: IC1.9, U4.13
/PLED1: D3.2, IC1.13
/PLED2: D4.2, IC1.14
/PLED3: D5.2, IC1.15
/RESET: IC1.31, P1.5, R16.2
/RXCAN: IC1.7, U3.4
/RX_SCK-P: IC1.12, P1.3
/SCK: IC1.28, U4.14
/SLAVE_SELECT: IC1.3, R17.2, U4.7
/TXCAN: IC1.6, U3.1
/TX_MOSI-P: IC1.2, P1.4
/XOUT: C13.1, IC1.17, R13.2
/YOUT: C14.1, IC1.18, R14.2
/ZOUT: C15.1, IC1.22, R15.2
GND: C1.2, C2.1, C3.2, C4.2, C5.2, C7.2, C8.2, C9.2, C10.2, C11.2, C12.2, C13.2, C14.2, C15.2, C16.2, C17.2, D1.2, D2.1, D6.1, IC1.5, IC1.20, J1.1, P1.6, R2.2, R4.2, R5.2, R7.2, R8.2, U1.5, U1.6, U1.7, U1.8, U2.1, U3.2, U3.8, U4.2, U4.4, U4.5, U5.2, U5.3, U5.5, U5.6, U5.7, Y1.2, Y1.4
unnamed: C3.1, C4.1, C5.1, F1.1, R3.1, R6.1, U2.3
unnamed: C6.1, U2.6
unnamed: C6.2, L1.1, U2.2
unnamed: C7.1, C8.1, C9.1, L1.2, R9.1, R10.2
unnamed: C12.1, IC1.19, R12.2
unnamed: C16.1, IC1.11, Y1.1
unnamed: C17.1, IC1.10, Y1.3
unnamed: D2.2, R3.2
unnamed: D3.1, R4.1
unnamed: D4.1, R5.1
unnamed: D5.1, R7.1
unnamed: D6.2, R11.2
unnamed: R1.2, R2.1, U1.3
unnamed: R6.2, U2.5
unnamed: R8.1, R9.2, U2.4
unnamed: R13.1, U5.12
unnamed: R14.1, U5.10
unnamed: R15.1, U5.8
VCC: C2.2, C10.1, C11.1, IC1.4, P1.2, R10.1, R11.1, R12.1, R16.1, R17.1, U1.1, U1.2, U3.3

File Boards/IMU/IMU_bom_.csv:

Part,References,Quantity Per PCB,MPN,MFN,PurchasingLink,MPN2,Webpage,Purchasing Link
C_0.1uF,C3 C6 C10 C11,4,478-3352-1-ND,Digi-Key,https://www.digikey.com/products/en?keywords=478-3352-1-ND,,,
C_0.33uF,C13 C14 C15,3,0805YC334J4T2A-ND,Digi-Key,https://www.digikey.com/products/en/capacitors/ceramic-capac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,,,
C_100pF,C12,1,399-1122-1-ND,Digi-Key,https://www.digikey.com/product-detail/en/kemet/C0805C101J5G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,,,
C_10uF,C1 C2 C4 C5,4,478-5167-1-ND,Digi-Key,https://www.digikey.com/product-detail/en/avx-corporation/08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,,,
C_22uF,C7 C8 C9,3,1276-2725-1-ND,Digi-Key,https://www.digikey.com/products/en?keywords=1276-2725-1-ND,,,
C_30pF,C16 C17,2,1276-1130-1-ND,Digi-Key,https://www.digikey.com/product-detail/en/samsung-electro-me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,,,
D_Zener_18V,D1,1,SMBJ5355B-TPMSCT-ND,Digi-Key,https://www.digikey.com/products/en?keywords=SMBJ5355B-TPMSCT-ND,,,
LED_0805,D2 D3 D4 D5 D6,5,475-1410-1-ND,Digi-Key,https://www.digikey.com/products/en?keywords=475-1410-1-ND,,,
F_500mA_16V,F1,1,507-1786-1-ND,Digi-Key,https://www.digikey.com/product-detail/en/bel-fuse-inc/0ZCH0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,,,
ATMEGA16M1,IC1,1,ATMEGA16M1-AU-ND,Digi-Key,https://www.digikey.com/product-detail/en/atmel/ATMEGA16M1-A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,,,
Ultrafit_4_RA,J1,1,WM11574-ND,Digi-Key,https://www.digikey.com/products/en?keywords=1723101304,WM11564-ND,,
L_4.7uH,L1,1,445-6583-1-ND,Digi-Key,https://www.digikey.com/product-detail/en/tdk-corporation/VL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,,,
CONN_02X03,P1,1,609-3234-ND,Digi-Key,https://www.digikey.com/product-detail/en/amphenol-fci/67997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,,,
R_0_Jumper,R10,1,A121322CT-ND,Digi-Key,https://www.digikey.com/products/en?keywords=A121322CT-ND,,,
R_100,R12,1,RNCP0805FTD100RCT-ND,Digi-Key,https://www.digikey.com/products/en?keywords=RNCP0805FTD100RCT-ND,,,
R_10k,R6 R8 R16 R17,4,CRS0805-FX-1002ELFCT-ND,Digi-Key,https://www.digikey.com/products/en?keywords=CRS0805-FX-1002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,,,
R_120k,R2,1,RMCF0805FT120KCT-ND,Digi-Key,https://www.digikey.com/product-detail/en/stackpole-electron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,,,
R_178k,R1,1,P178KDATR-ND,Digikey,https://www.digikey.com/product-detail/en/stackpole-electron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,,https://www.digikey.com/product-detail/en/panasonic-electron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,
R_1k,R3,1,RNCP0805FTD1K00CT-ND,Digi-Key,https://www.digikey.com/products/en?keywords=RNCP0805FTD1K00CT-ND,,,
R_200,R4 R5 R7 R11,4,RMCF0805JT200RCT-ND,Digi-Key,https://www.digikey.com/products/en?keywords=RMCF0805JT200RCT-ND,,,
R_30.1k,R13 R14 R15,3,,,https://www.digikey.com/product-detail/en/stackpole-electron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,,,
R_55.1k,R9,1,311-51.1KCRCT-ND,Digi-Key,https://www.digikey.com/products/en?keywords=311-51.1KCRCT-ND,,,
ADXL335,U5,1,,,https://www.digikey.com/product-detail/en/analog-devices-inc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,,,
ADXL345,U4,1,,,https://www.digikey.com/product-detail/en/analog-devices-inc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,,,
CAN_Transceiver,U3,1,MCP2561-E/SN-ND,Digi-Key,https://www.digikey.com/products/en?keywords=mcp2561-e%2Fsn,,,
L693D1,U1,1,,,,,,https://www.digikey.com/product-detail/en/stmicroelectronics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
TPS561201,U2,1,TPS561201,Digi-Key,https://www.digikey.com/products/en?keywords=296-46928-1-ND,,,
Crystal_SMD,Y1,1,SER3686CT-ND,Digi-Key,https://www.digikey.com/products/en?keywords=SER3686CT-ND,,,

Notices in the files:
parts and their libraries:
Copyright 2016 Accelerated Designs. All rights reserved.
